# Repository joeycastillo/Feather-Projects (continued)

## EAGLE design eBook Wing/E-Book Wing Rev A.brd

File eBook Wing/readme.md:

**DO NOT USE THIS! [Use this instead](https://github.com/joeycastillo/The-Open-Book)**

# E-Book Wing README

This was the first attempt to make a DIY device for reading books, but revision A had a couple of crucial design flaws. You can cut some traces and add some wires to make this board work, but more likely you'll want to use revision B, which can be found in [the Open Book repo](https://github.com/joeycastillo/The-Open-Book).

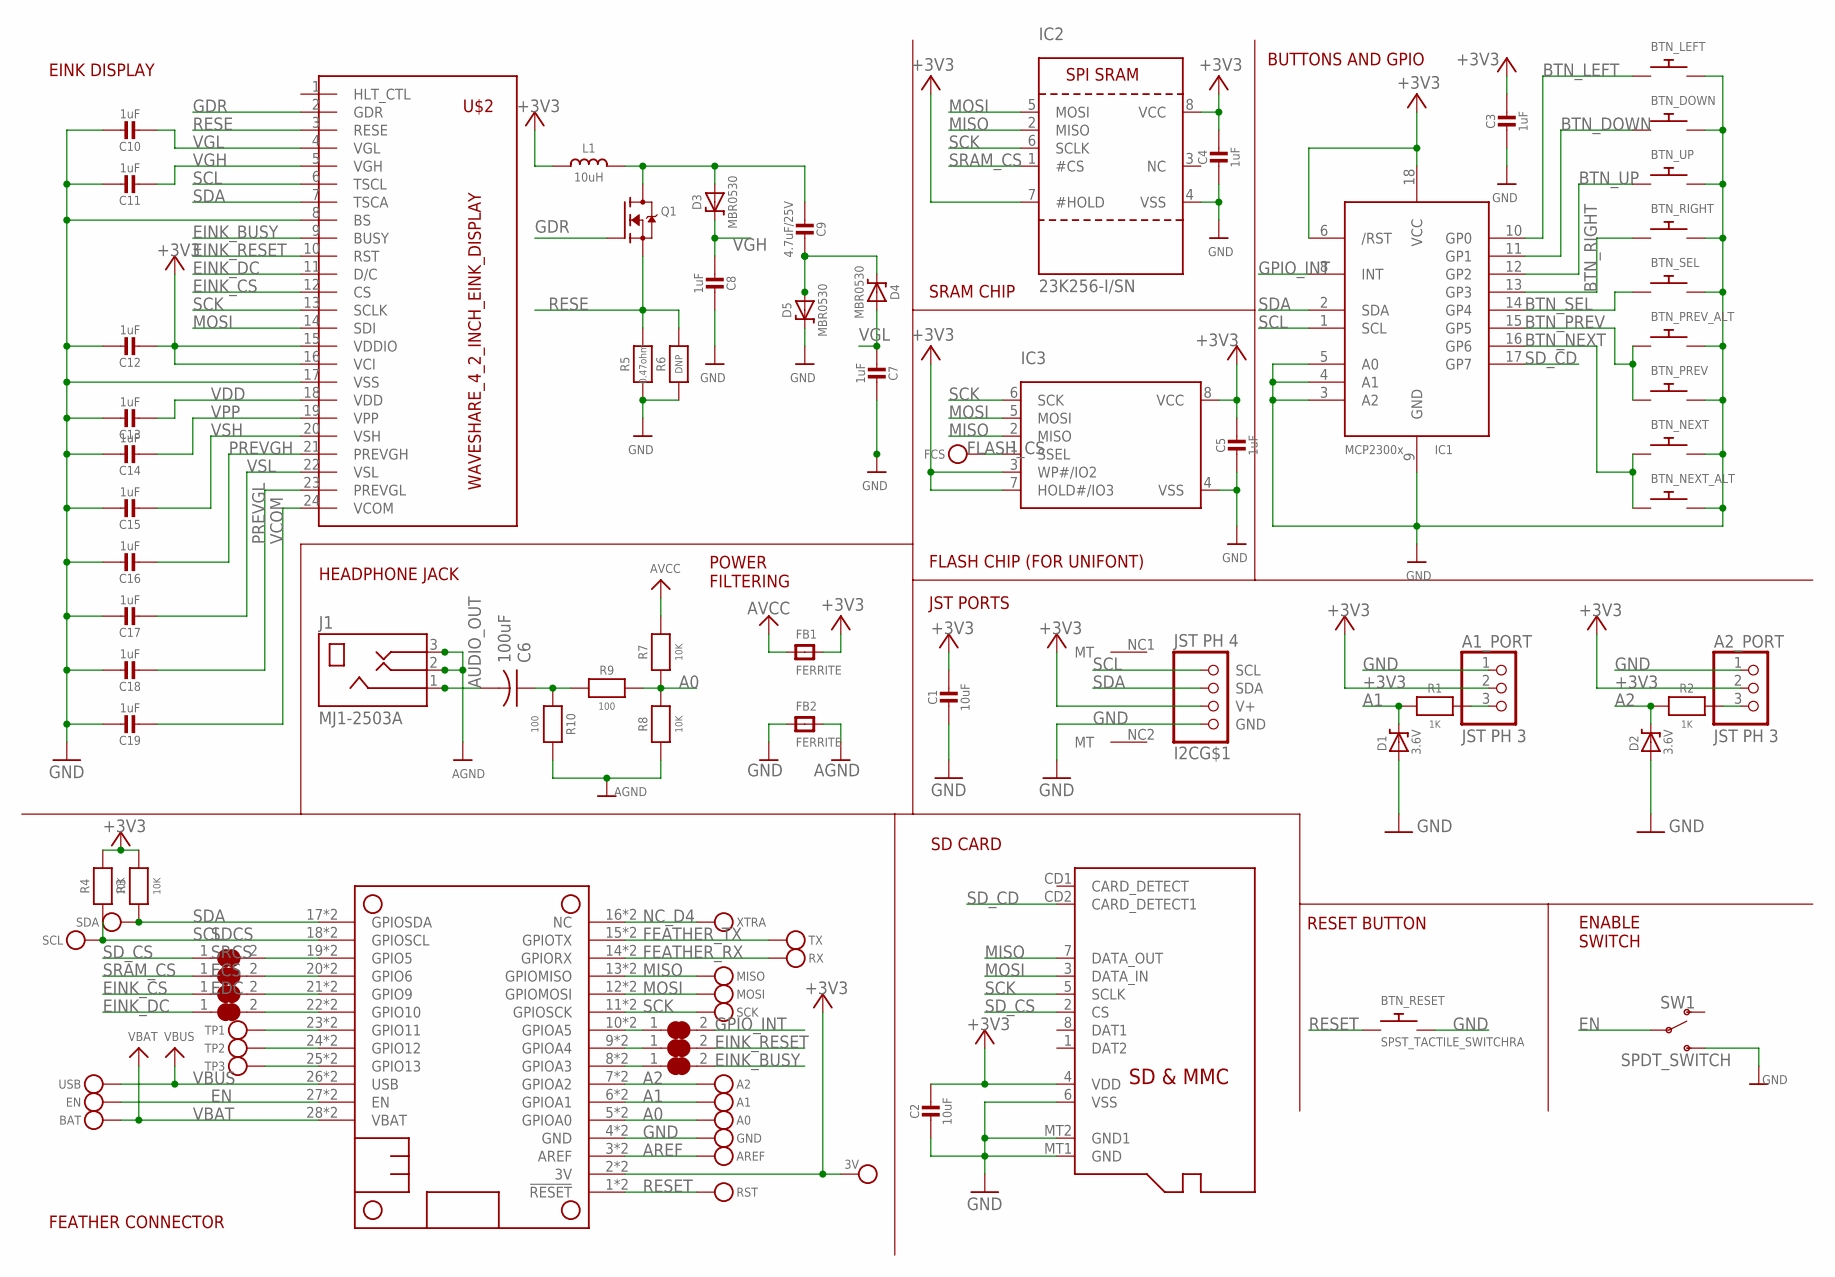
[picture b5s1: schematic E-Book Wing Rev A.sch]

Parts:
3V: MICROBUILDER_TESTPOINT1.5X2.0MM_NOCREAM; MICROBUILDER_PAD-1.5X2.0
A0, A1, A2: MICROBUILDER_TESTPOINT1.5X2.0MM_NOCREAM; MICROBUILDER_PAD-1.5X2.0
A1_PORT, A2_PORT: JST PH 3; JSTPH3
AREF: MICROBUILDER_TESTPOINT1.5X2.0MM_NOCREAM; MICROBUILDER_PAD-1.5X2.0
BAT: MICROBUILDER_TESTPOINT1.5X2.0MM_NOCREAM; MICROBUILDER_PAD-1.5X2.0
BTN_DOWN: MJTP1250_SPST_SWITCH; MJTP1250
BTN_LEFT: MJTP1250_SPST_SWITCH; MJTP1250
BTN_NEXT: MJTP1250_SPST_SWITCH; MJTP1250
BTN_NEXT_ALT: SPST_TACTILE_SWITCHRA; TL3330AF130QG
BTN_PREV: MJTP1250_SPST_SWITCH; MJTP1250
BTN_PREV_ALT: SPST_TACTILE_SWITCHRA; TL3330AF130QG
BTN_RESET: SPST_TACTILE_SWITCHRA; TL3330AF130QG
BTN_RIGHT: MJTP1250_SPST_SWITCH; MJTP1250
BTN_SEL: MJTP1250_SPST_SWITCH; MJTP1250
BTN_UP: MJTP1250_SPST_SWITCH; MJTP1250
C1: 10uF; 0805-NO
C2: 10uF; 0805_10MGAP
C3, C4, C5: 1uF; 0805_10MGAP
C6: 100uF; C1210
C7, C8, C10, C11, C12, C13, C14, C15, C16, C17, C18, C19: 1uF; 0805-NO
C9: 4.7uF/25V; 0805-NO
D1, D2: 3.6V; SOD-123
D3, D4, D5: MBR0530; SOD-123
EBSY: MICROBUILDER_SOLDERJUMPER_CLOSED; MICROBUILDER_SOLDERJUMPER_CLOSEDWIRE
ECS: MICROBUILDER_SOLDERJUMPER_CLOSED; MICROBUILDER_SOLDERJUMPER_CLOSEDWIRE
EDC: MICROBUILDER_SOLDERJUMPER_CLOSED; MICROBUILDER_SOLDERJUMPER_CLOSEDWIRE
EN: MICROBUILDER_TESTPOINT1.5X2.0MM_NOCREAM; MICROBUILDER_PAD-1.5X2.0
ERST: MICROBUILDER_SOLDERJUMPER_CLOSED; MICROBUILDER_SOLDERJUMPER_CLOSEDWIRE
FB1, FB2: FERRITE; 0805
FCS: MICROBUILDER_TESTPOINTPAD1MM; MICROBUILDER_TESTPOINT_PAD_1MM
GND: MICROBUILDER_TESTPOINT1.5X2.0MM_NOCREAM; MICROBUILDER_PAD-1.5X2.0
I2C: JST PH 4; JSTPH4
IC1: MCP23008/SO; SO18W
IC2: 23K256-I/SN; SOIC8_150MIL
IC3: MICROBUILDER_SPIFLASH_SOIC8; MICROBUILDER_SOIC8_150MIL
INT: MICROBUILDER_SOLDERJUMPER_CLOSED; MICROBUILDER_SOLDERJUMPER_CLOSEDWIRE
J1: MJ1-2503A; CUI_MJ1-2503A
L1: 10uH; INDUCTOR_4X4MM_NR401
MICROSD: MICROSD
MISO: MICROBUILDER_TESTPOINT1.5X2.0MM_NOCREAM; MICROBUILDER_PAD-1.5X2.0
MOSI: MICROBUILDER_TESTPOINT1.5X2.0MM_NOCREAM; MICROBUILDER_PAD-1.5X2.0
MS1: MICROBUILDER_FEATHERWING_SMTDUAL; MICROBUILDER_FEATHERWING_SMT2
Q1: IRLML0100; SOT23-3
R1, R2: 1K; _0805MP
R3, R4, R7, R8: 10K; _0805MP
R5: 0.47ohm; 0805_10MGAP
R6: DNP; 0805_10MGAP
R9, R10: 100; _0805MP
RST: MICROBUILDER_TESTPOINT1.5X2.0MM_NOCREAM; MICROBUILDER_PAD-1.5X2.0
RX: MICROBUILDER_TESTPOINT1.5X2.0MM_NOCREAM; MICROBUILDER_PAD-1.5X2.0
SCK: MICROBUILDER_TESTPOINT1.5X2.0MM_NOCREAM; MICROBUILDER_PAD-1.5X2.0
SCL: MICROBUILDER_TESTPOINT1.5X2.0MM_NOCREAM; MICROBUILDER_PAD-1.5X2.0
SDA: MICROBUILDER_TESTPOINT1.5X2.0MM_NOCREAM; MICROBUILDER_PAD-1.5X2.0
SDCS: MICROBUILDER_SOLDERJUMPER_CLOSED; MICROBUILDER_SOLDERJUMPER_CLOSEDWIRE
SRCS: MICROBUILDER_SOLDERJUMPER_CLOSED; MICROBUILDER_SOLDERJUMPER_CLOSEDWIRE
SW1: SPDT_SWITCH; A10767
TP1, TP2, TP3: MICROBUILDER_TESTPOINT1.5X2.0MM_NOCREAM; MICROBUILDER_PAD-1.5X2.0
TX: MICROBUILDER_TESTPOINT1.5X2.0MM_NOCREAM; MICROBUILDER_PAD-1.5X2.0
U$2: WAVESHARE_4_2_INCH_EINK_DISPLAY; EINK_DISPLAY_4_2IN
USB: MICROBUILDER_TESTPOINT1.5X2.0MM_NOCREAM; MICROBUILDER_PAD-1.5X2.0
XTRA: MICROBUILDER_TESTPOINT1.5X2.0MM_NOCREAM; MICROBUILDER_PAD-1.5X2.0

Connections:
+3V3: 3V.P$1, A1_PORT.2, A2_PORT.2, C1.1, C2.1, C3.1, C4.1, C5.1, C12.2, FB1.2, I2C.2 (V+), IC1.6 (/RST), IC1.18 (VCC), IC2.7 (#HOLD), IC2.8 (VCC), IC3.3 (WP#/IO2), IC3.7 (HOLD#/IO3), IC3.8 (VCC), L1.P$2 (2), MICROSD.4 (VDD), MS1.2 (3V), MS1.2' (3V), R3.1, R4.1, U$2.15 (VDDIO), U$2.16 (VCI)
A0: A0.P$1, MS1.5 (GPIOA0), MS1.5' (GPIOA0), R7.2, R8.1, R9.1
A1: A1.P$1, D1.C, MS1.6 (GPIOA1), MS1.6' (GPIOA1), R1.2
A1_: A1_PORT.3, R1.1
A2: A2.P$1, D2.C, MS1.7 (GPIOA2), MS1.7' (GPIOA2), R2.2
A2_: A2_PORT.3, R2.1
AGND: FB2.2, J1.2, J1.3, R8.2, R10.1
AREF: AREF.P$1, MS1.3 (AREF), MS1.3' (AREF)
AUDIO_OUT: C6.2, J1.1
AVCC: FB1.1, R7.1
BTN_DOWN: BTN_DOWN.P$1, IC1.11 (GP1)
BTN_LEFT: BTN_LEFT.P$1, IC1.10 (GP0)
BTN_NEXT: BTN_NEXT.P$1, BTN_NEXT_ALT.P$1, IC1.16 (GP6)
BTN_PREV: BTN_PREV.P$1, BTN_PREV_ALT.P$1, IC1.15 (GP5)
BTN_RIGHT: BTN_RIGHT.P$1, IC1.13 (GP3)
BTN_SEL: BTN_SEL.P$1, IC1.14 (GP4)
BTN_UP: BTN_UP.P$1, IC1.12 (GP2)
EINK_BUSY: EBSY.2, U$2.9 (BUSY)
EINK_CS: ECS.1, U$2.12 (CS)
EINK_DC: EDC.1, U$2.11 (D/C)
EINK_RESET: ERST.2, U$2.10 (RST)
EN: EN.P$1, MS1.27 (EN), MS1.27' (EN), SW1.P$2
FEATHER_RX: MS1.14 (GPIORX), MS1.14' (GPIORX), RX.P$1
FEATHER_TX: MS1.15 (GPIOTX), MS1.15' (GPIOTX), TX.P$1
FLASH_CS: FCS.P$1, IC3.1 (SSEL)
GDR: Q1.1 (G), U$2.2 (GDR)
GND: A1_PORT.1, A2_PORT.1, BTN_DOWN.P$2, BTN_LEFT.P$2, BTN_NEXT.P$2, BTN_NEXT_ALT.P$2, BTN_PREV.P$2, BTN_PREV_ALT.P$2, BTN_RESET.P$2, BTN_RIGHT.P$2, BTN_SEL.P$2, BTN_UP.P$2, C1.2, C2.2, C3.2, C4.2, C5.2, C7.2, C8.2, C10.1, C11.1, C12.1, C13.1, C14.1, C15.1, C16.1, C17.1, C18.1, C19.1, D1.A, D2.A, D5.C, FB2.1, GND.P$1, I2C.1 (GND), IC1.3 (A2), IC1.4 (A1), IC1.5 (A0), IC1.9 (GND), IC2.4 (VSS), IC3.4 (VSS), MICROSD.6 (VSS), MICROSD.MT1 (GND), MICROSD.MT2 (GND1), MS1.4 (GND), MS1.4' (GND), R5.2, R6.2, SW1.P$3 (S), U$2.8 (BS), U$2.17 (VSS)
GPIO_INT: IC1.8 (INT), INT.2
MISO: IC2.2 (MISO), IC3.2 (MISO), MICROSD.7 (DATA_OUT), MISO.P$1, MS1.13 (GPIOMISO), MS1.13' (GPIOMISO)
MOSI: IC2.5 (MOSI), IC3.5 (MOSI), MICROSD.3 (DATA_IN), MOSI.P$1, MS1.12 (GPIOMOSI), MS1.12' (GPIOMOSI), U$2.14 (SDI)
unnamed: C6.1, R9.2, R10.2
unnamed: C9.2, D4.C, D5.A
unnamed: C9.1, D3.A, L1.P$1 (1), Q1.3 (D)
unnamed: MS1.25 (GPIO13), MS1.25' (GPIO13), TP3.P$1
unnamed: MS1.24 (GPIO12), MS1.24' (GPIO12), TP2.P$1
unnamed: MS1.23 (GPIO11), MS1.23' (GPIO11), TP1.P$1
NC_D4: MS1.16 (NC), MS1.16' (NC), XTRA.P$1
PREVGH: C16.2, U$2.21 (PREVGH)
PREVGL: C18.2, U$2.23 (PREVGL)
RESE: Q1.2 (S), R5.1, R6.1, U$2.3 (RESE)
RESET: BTN_RESET.P$1, MS1.1 (!RESET), MS1.1' (!RESET), RST.P$1
SCK: IC2.6 (SCLK), IC3.6 (SCK), MICROSD.5 (SCLK), MS1.11 (GPIOSCK), MS1.11' (GPIOSCK), SCK.P$1, U$2.13 (SCLK)
SCL: I2C.4 (SCL), IC1.1 (SCL), MS1.18 (GPIOSCL), MS1.18' (GPIOSCL), R4.2, SCL.P$1, U$2.6 (TSCL)
SDA: I2C.3 (SDA), IC1.2 (SDA), MS1.17 (GPIOSDA), MS1.17' (GPIOSDA), R3.2, SDA.P$1, U$2.7 (TSCA)
SD_CD: IC1.17 (GP7), MICROSD.CD2 (CARD_DETECT1)
SD_CS: MICROSD.2 (CS), SDCS.1
SRAM_CS: IC2.1 (#CS), SRCS.1
VBAT: BAT.P$1, MS1.28 (VBAT), MS1.28' (VBAT)
VBUS: MS1.26 (USB), MS1.26' (USB), USB.P$1
VCOM: C19.2, U$2.24 (VCOM)
VDD: C13.2, U$2.18 (VDD)
VGH: C8.1, C11.2, D3.C, U$2.5 (VGH)
VGL: C7.1, C10.2, D4.A, U$2.4 (VGL)
VPP: C14.2, U$2.19 (VPP)
VSH: C15.2, U$2.20 (VSH)
VSL: C17.2, U$2.22 (VSL)
_EINK_BUSY: EBSY.1, MS1.8 (GPIOA3), MS1.8' (GPIOA3)
_EINK_CS: ECS.2, MS1.21 (GPIO9), MS1.21' (GPIO9)
_EINK_DC: EDC.2, MS1.22 (GPIO10), MS1.22' (GPIO10)
_EINK_RESET: ERST.1, MS1.9 (GPIOA4), MS1.9' (GPIOA4)
_GPIO_INT: INT.1, MS1.10 (GPIOA5), MS1.10' (GPIOA5)
_SD_CS: MS1.19 (GPIO5), MS1.19' (GPIO5), SDCS.2
_SRAM_CS: MS1.20 (GPIO6), MS1.20' (GPIO6), SRCS.2

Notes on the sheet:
FEATHER CONNECTOR
SD CARD
EINK DISPLAY
HEADPHONE JACK
RESET BUTTON
ENABLE SWITCH
POWER FILTERING
BUTTONS AND GPIO
JST PORTS
SRAM CHIP
FLASH CHIP (FOR UNIFONT)

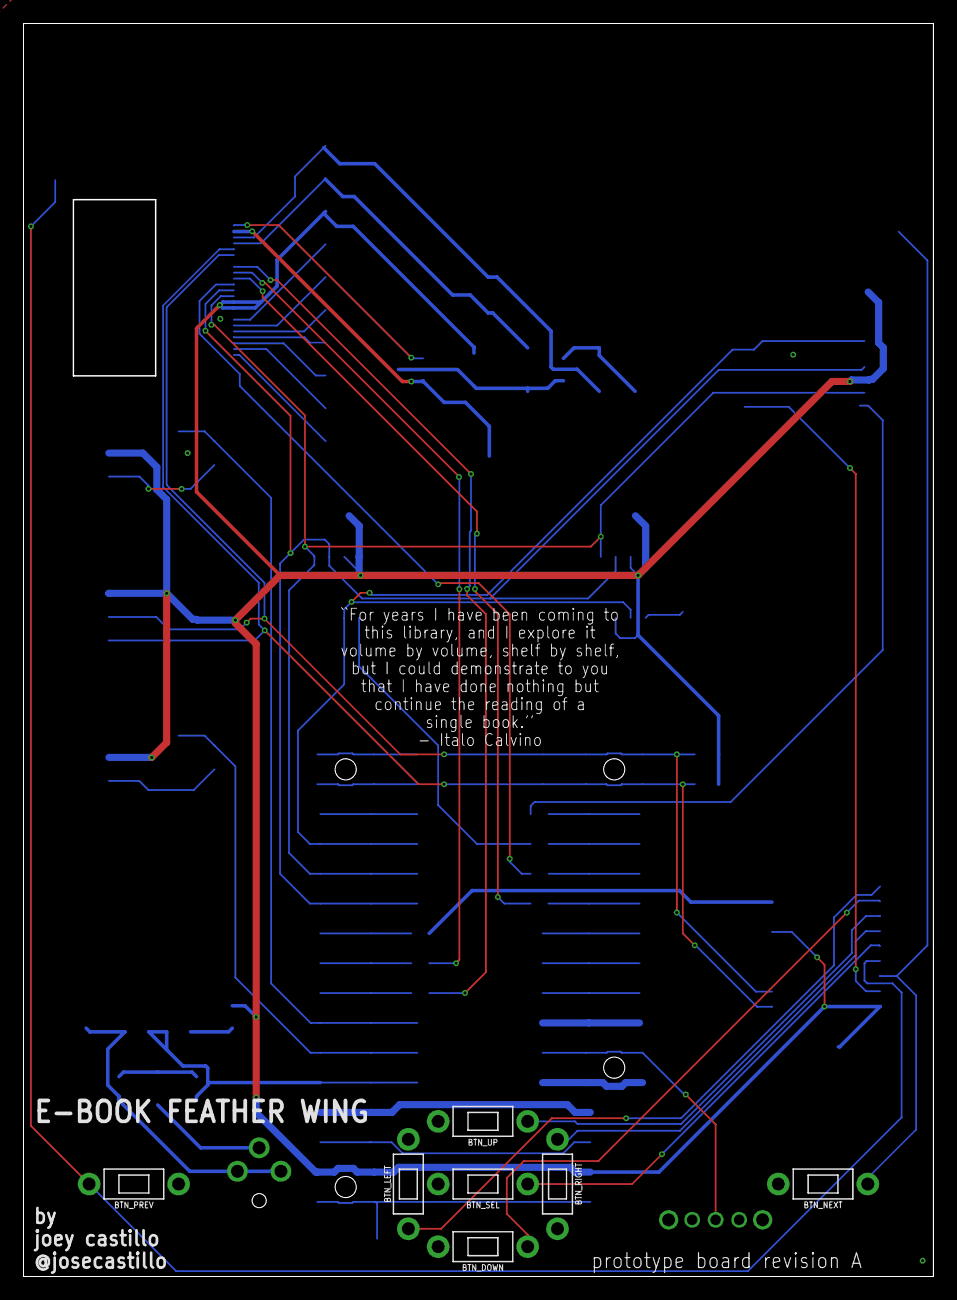
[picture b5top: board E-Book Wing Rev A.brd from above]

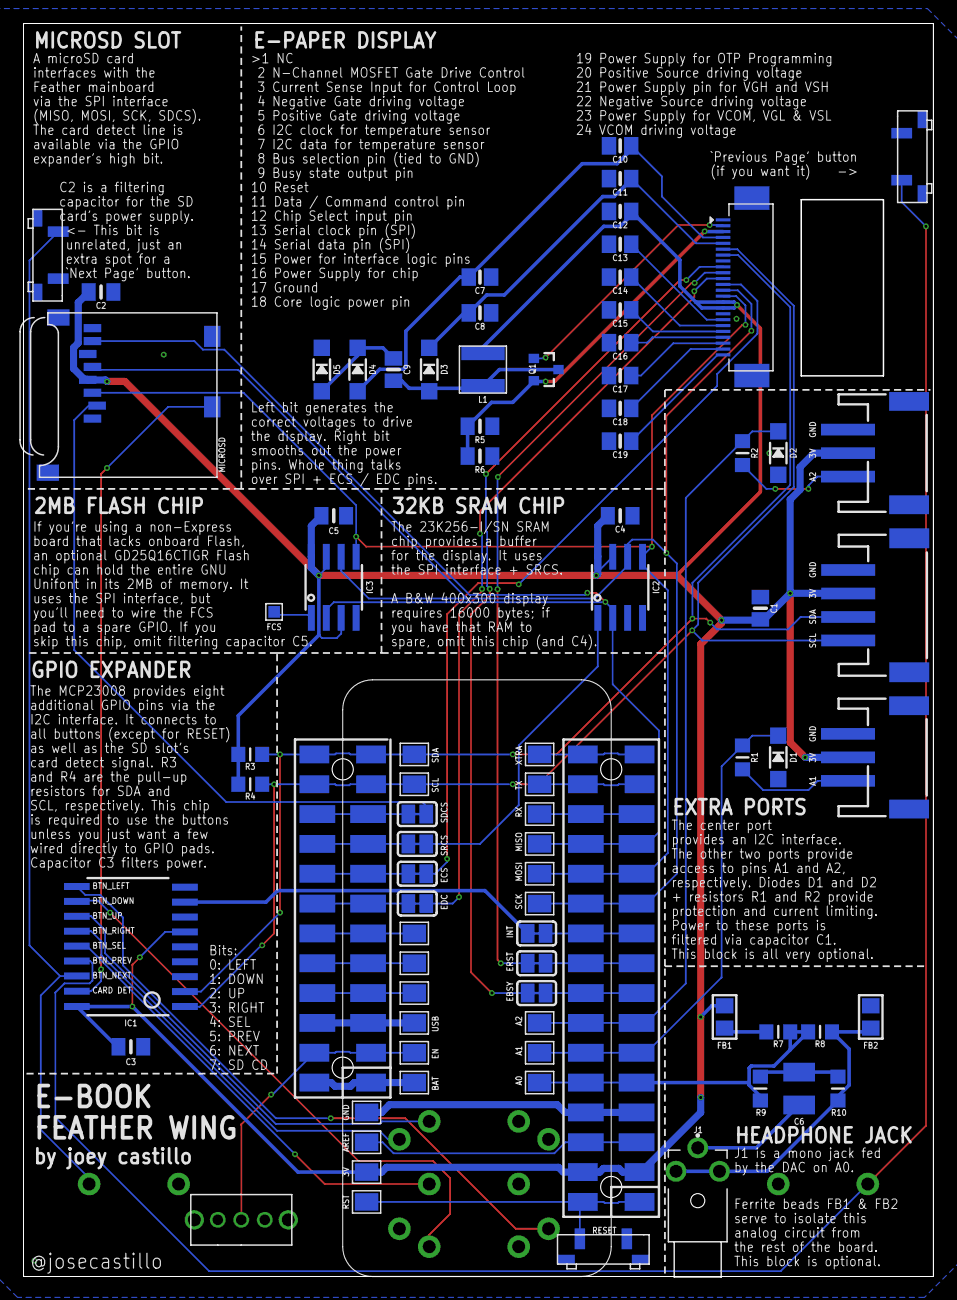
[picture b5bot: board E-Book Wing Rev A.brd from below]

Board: 2 copper layers, 77.5 x 106.7 mm, 88 parts (80 on the bottom side), 63 nets.
